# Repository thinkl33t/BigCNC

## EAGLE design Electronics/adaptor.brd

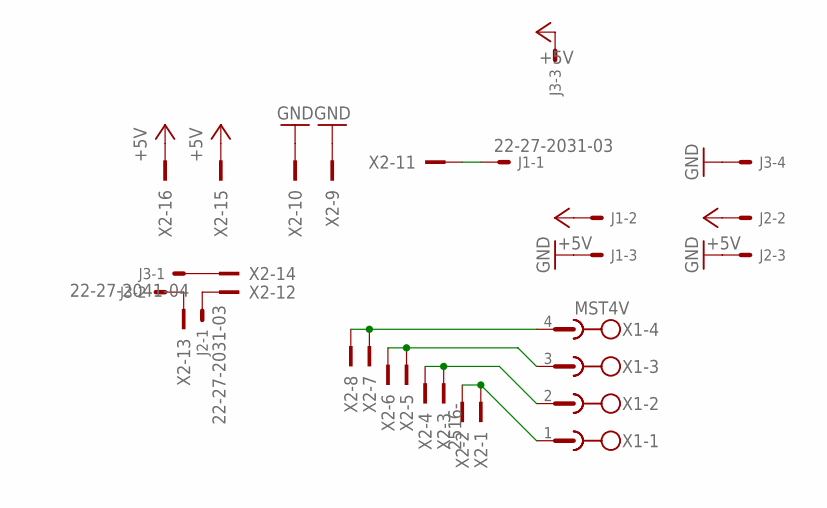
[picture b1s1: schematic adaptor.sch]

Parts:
J1, J2: 22-27-2031-03; 6410-03
J3: 22-27-2041-04; 6410-04
X1: MST4V; MSTBV4
X2: 2516-; PAK100/2500-16

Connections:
+5V: J1.2, J2.2, J3.3, X2.15, X2.16
GND: J1.3, J2.3, J3.4, X2.9, X2.10
unnamed: X1.4, X2.7, X2.8
unnamed: X1.3, X2.5, X2.6
unnamed: X1.2, X2.3, X2.4
unnamed: X1.1, X2.1, X2.2
unnamed: J1.1, X2.11
unnamed: J3.1, X2.14
unnamed: J2.1, X2.12
unnamed: J3.2, X2.13

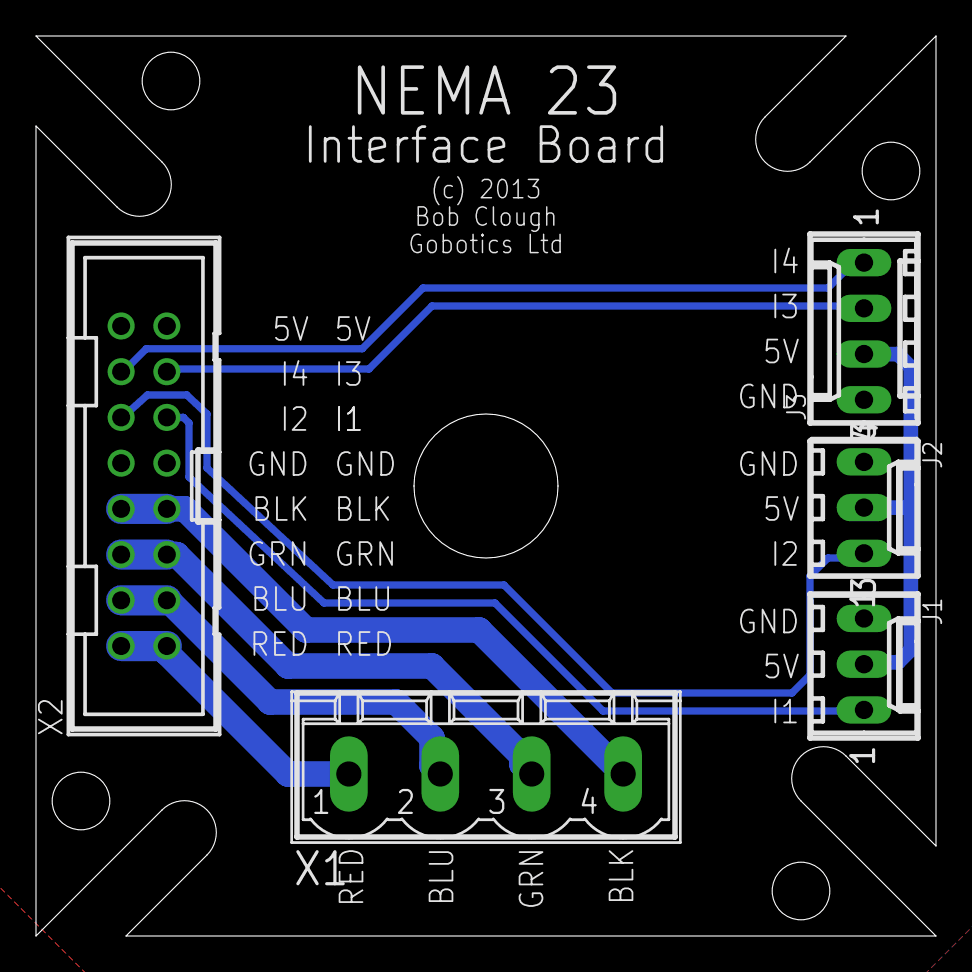
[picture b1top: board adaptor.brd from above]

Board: 2 copper layers, 50.0 x 50.0 mm, 5 parts (0 on the bottom side), 10 nets.

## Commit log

2014-11-06 Added v0.1 of BigCNC
2015-03-13 Began mockup of axis' linear actuator system
2015-03-18 Axis basic thrust ends etc
2015-03-18 Added redesigned thrust ends.

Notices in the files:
Electronics/adaptor.brd:
(c) 2013
